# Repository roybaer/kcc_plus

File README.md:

# KCC plus - a new, enhanced, CPC6128 compatible home computer

**WORK IN PROGRESS**

The _KCC plus_ is a retroactively designed hypothetical early 1990s successor to the KC compact.
The KC compact was a largely compatible clone of the Amstrad CPC 6128, built without custom silicon.

Once completed, it can be considered a cousin of, but not a clone of the Amstrad 6128 Plus.

## Planned feature set

The following hardware features are currently planned

- Between 256 KiB and 1024 KiB of RAM, ideally as a pair of SRAM chips
- Two AY-2-8910 PSGs for additional polyphony and additional control lines, on-board Digiblaster
- 16 bit data path for pixel generation and duplication of the relevant logic for twice the color depth
- Bypassable EGA-like latch in the second RAM chip's data path to keep block fill/copy operations fast
- At least one attribute mode, e.g. for colorful high-res pseudo text modes
- Possibility to optionally double the CPU clock and/or FDC clock, if feasible
- Floppy disk and tape interface
- Internal IDE and Serial ports, if feasible
- The CPC 6128's form factor: System board should fit inside a German CPC 6128 case
- High quality keyboard with n-key rollover
- 50-pin micro ribbon expansion port
- Bi-directional 8-bit printer port (DB25)
- DIN and SCART video output and 3.5 mm audio line-out
- Two digital joystick ports
- Light pen connector
- Laser-cut case, e.g. painted plywood

## Hardware components

These hardware components have been completed

- [Keyboard assembly](kcc_plus_keyboard/README.md) using the CPC 6128 form factor

These hardware components are planned

- Feature evaluation module for CPC
  - Clock generation and audio board
  - RAM and video board
  - Mass storage board
- System board
- Laser-cut case

## License

All design files contained herein may be redistributed and/or modified under the terms of the CERN-OHL-P license.

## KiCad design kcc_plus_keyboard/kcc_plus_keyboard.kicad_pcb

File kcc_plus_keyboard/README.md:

# KCC plus - keyboard assembly

This is a mechanical keyboard for the KCC plus.
It uses a CPC 6128 compatible form factor and keyboard matrix.

# Layout

The following layout is recommended for contemporary English.
Suitable off-the-shelf keycap sets are available.

| Switch    | Glyph     | Switch    | Glyph
|:----------|:----------|:----------|:----------
| SW1       | Esc       | SW39      | F
| SW2       | 1         | SW40      | G
| SW3       | 2         | SW41      | H
| SW4       | 3         | SW42      | J
| SW5       | 4         | SW43      | K
| SW6       | 5         | SW44      | L
| SW7       | 6         | SW45      | ;
| SW8       | 7         | SW46      | '
| SW9       | 8         | SW47      | '
| SW10      | 9         | SW48      | F1
| SW11      | 0         | SW49      | F2
| SW12      | -         | SW50      | F3
| SW13      | =         | SW51      | shift
| SW14      | backspace | SW52      | Z
| SW15      | F7        | SW53      | X
| SW16      | F8        | SW54      | C
| SW17      | F9        | SW55      | V
| SW18      | tab       | SW56      | B
| SW19      | Q         | SW57      | N
| SW20      | W         | SW58      | M
| SW21      | E         | SW59      | ,
| SW22      | R         | SW60      | .
| SW23      | T         | SW61      | /
| SW24      | Y         | SW62      | \
| SW25      | U         | SW63      | shift
| SW26      | I         | SW64      | F10
| SW27      | O         | SW65      | ↑ (up)
| SW28      | P         | SW66      | .
| SW29      | [         | SW67      | control
| SW30      | ]         | SW68      | option
| SW31      | return    | SW69      | command
| SW32      | F4        | SW70      | space
| SW33      | F5        | SW71      | command
| SW34      | F6        | SW72      | del
| SW35      | capslock  | SW73      | enter
| SW36      | A         | SW74      | ← (left)
| SW37      | S         | SW75      | ↓ (down)
| SW38      | D         | SW76      | → (right)

## Pictures

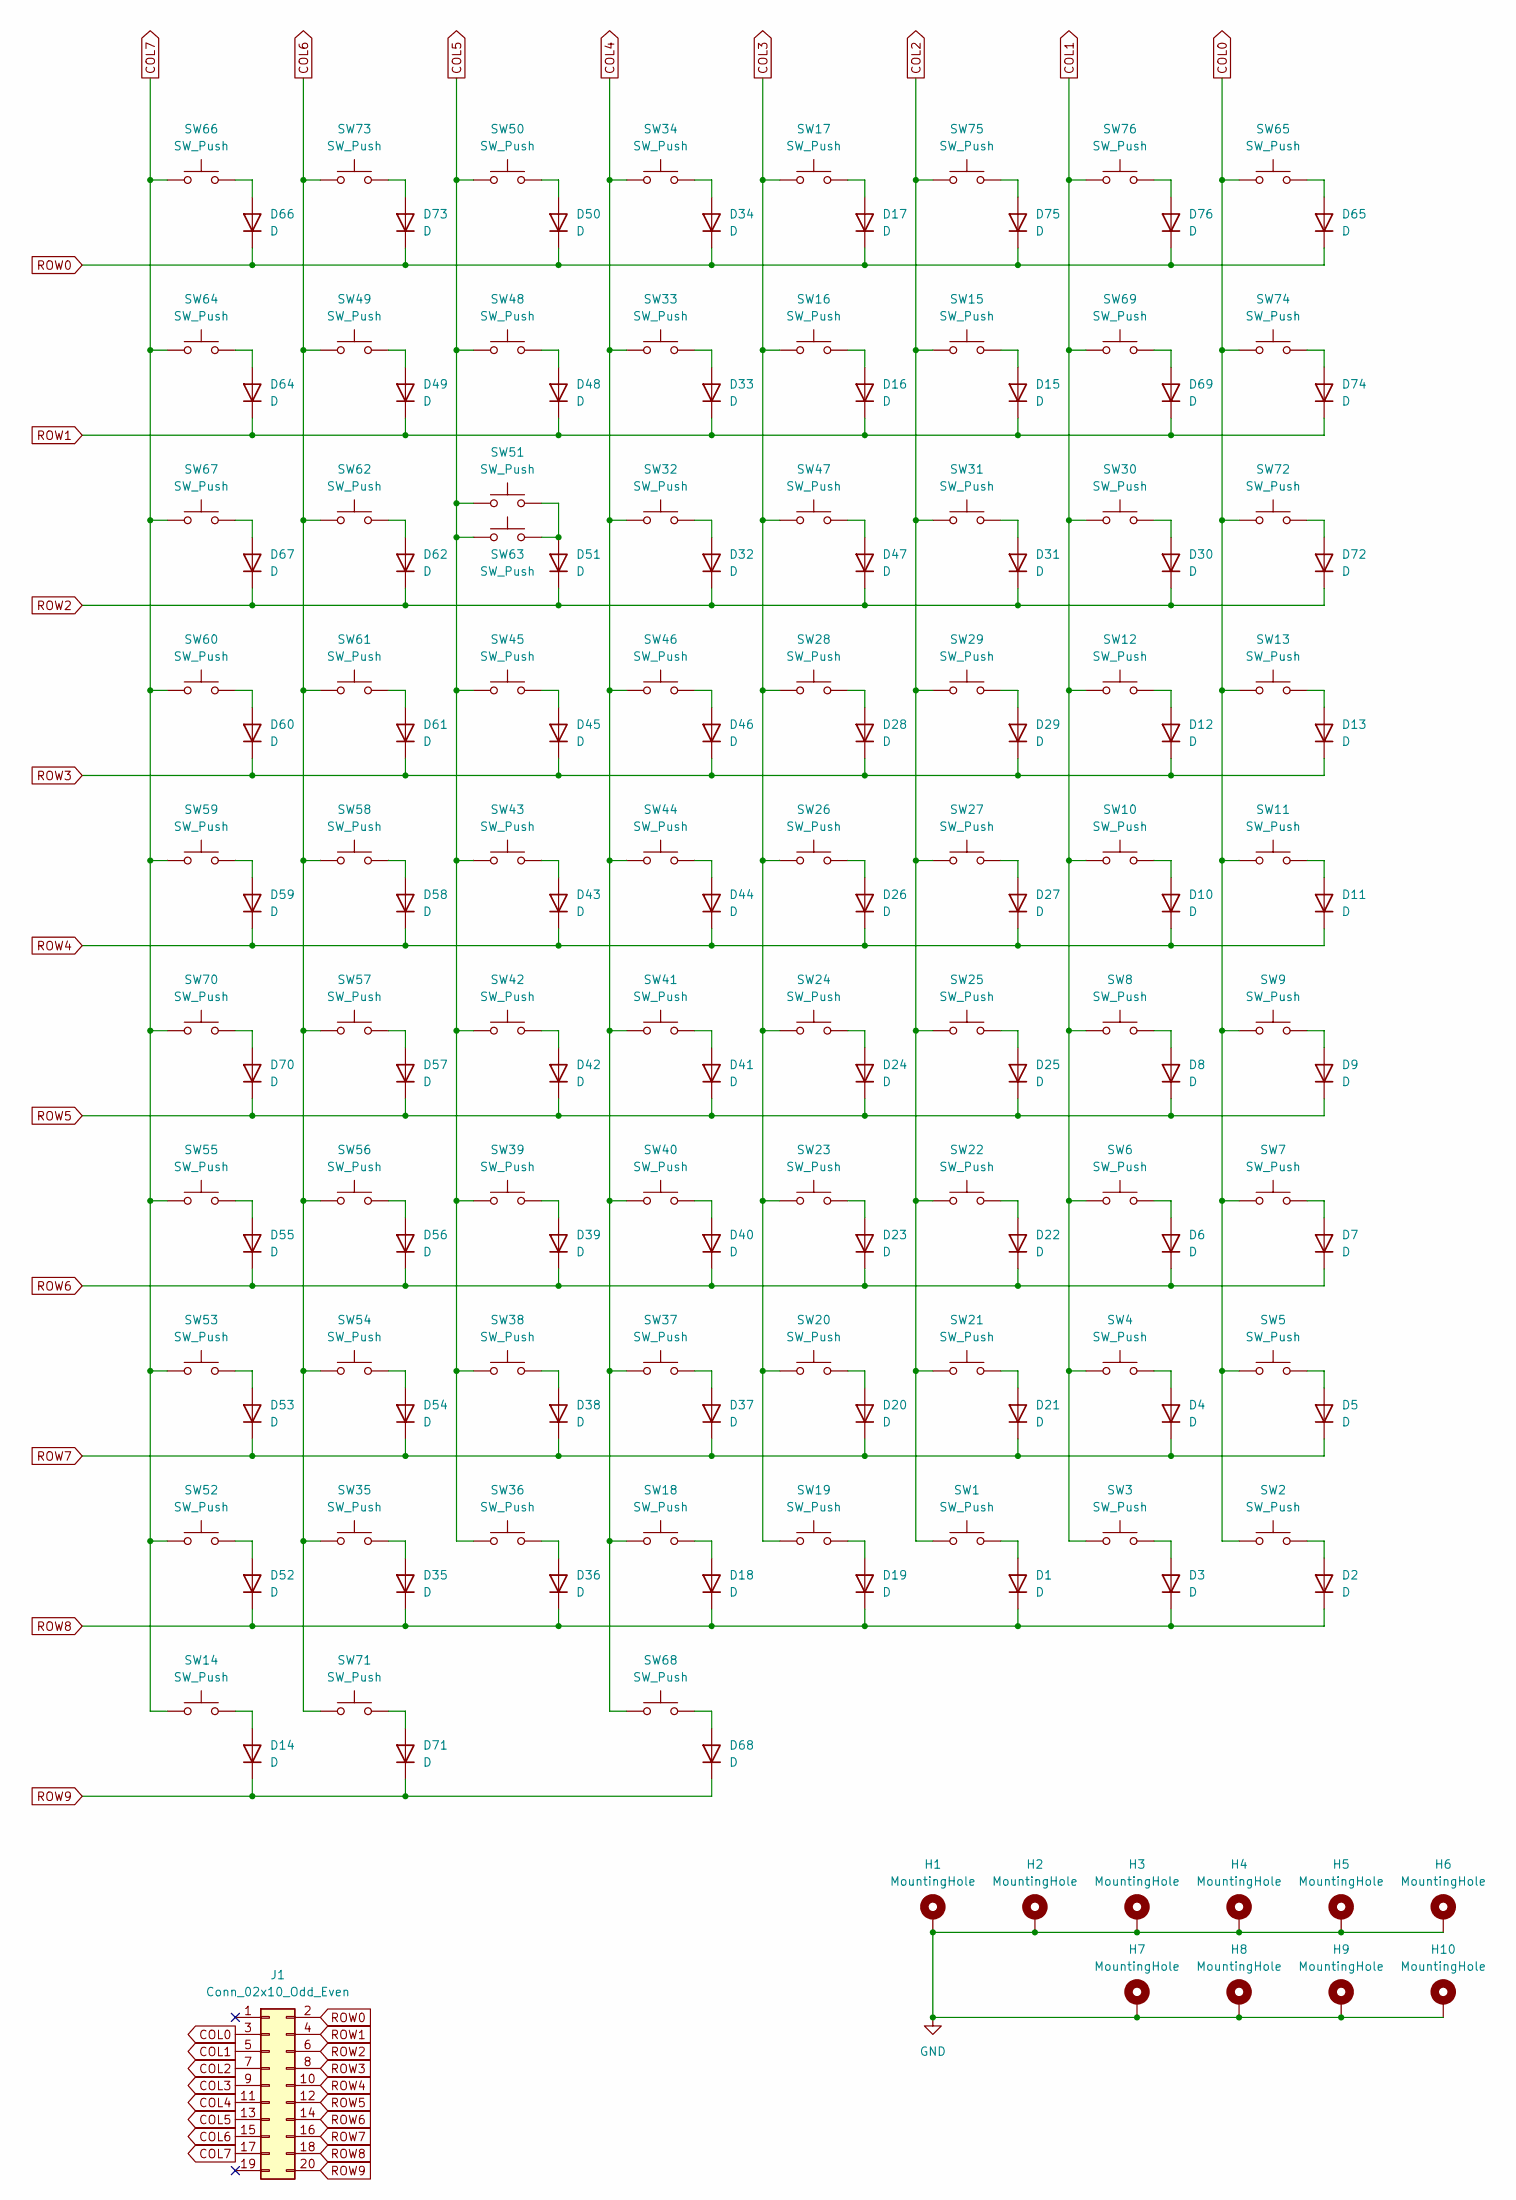
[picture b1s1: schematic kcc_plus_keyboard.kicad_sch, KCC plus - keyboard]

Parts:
D1, D2, D3, D4, D5, D6, D7, D8, D9, D10, D11, D12, D13, D14, D15, D16, D17, D18, D19, D20, D21, D22, D23, D24, D25, D26, D27, D28, D29, D30, D31, D32, D33, D34, D35, D36, D37, D38, D39, D40, D41, D42, D43, D44, D45, D46, D47, D48, D49, D50, D51, D52, D53, D54, D55, D56, D57, D58, D59, D60, D61, D62, D64, D65, D66, D67, D68, D69, D70, D71, D72, D73, D74, D75, D76: D; D_DO-35_SOD27_P7.62mm_Horizontal
H1, H3, H4, H6: MountingHole; MountingHole_4.3x6.2mm_M4_Pad_Via
H2, H5, H7, H8, H9, H10: MountingHole; MountingHole_4.3mm_M4_Pad_Via
J1: Conn_02x10_Odd_Even; PinHeader_2x10_P2.54mm_Horizontal
SW1, SW2, SW3, SW4, SW5, SW6, SW7, SW8, SW9, SW10, SW11, SW12, SW13, SW15, SW16, SW17, SW19, SW20, SW21, SW22, SW23, SW24, SW25, SW26, SW27, SW28, SW29, SW30, SW32, SW33, SW34, SW36, SW37, SW38, SW39, SW40, SW41, SW42, SW43, SW44, SW45, SW46, SW47, SW48, SW49, SW50, SW52, SW53, SW54, SW55, SW56, SW57, SW58, SW59, SW60, SW61, SW62, SW64, SW65, SW66, SW72, SW74, SW75, SW76: SW_Push; SW_Cherry_MX_1.00u_PCB
SW14: SW_Push; SW_Cherry_MX_2.00u_PCB
SW18, SW69, SW71: SW_Push; SW_Cherry_MX_1.50u_PCB
SW31: SW_Push; SW_Cherry_MX_ISOEnter_PCB
SW35, SW63: SW_Push; SW_Cherry_MX_1.75u_PCB
SW51, SW73: SW_Push; SW_Cherry_MX_2.25u_PCB
SW67, SW68: SW_Push; SW_Cherry_MX_1.25u_PCB
SW70: SW_Push; SW_Cherry_MX_6.25u_PCB

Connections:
COL0: J1.3, SW2.1, SW5.1, SW7.1, SW9.1, SW11.1, SW13.1, SW65.1, SW72.1, SW74.1
COL1: J1.5, SW3.1, SW4.1, SW6.1, SW8.1, SW10.1, SW12.1, SW30.1, SW69.1, SW76.1
COL2: J1.7, SW1.1, SW15.1, SW21.1, SW22.1, SW25.1, SW27.1, SW29.1, SW31.1, SW75.1
COL3: J1.9, SW16.1, SW17.1, SW19.1, SW20.1, SW23.1, SW24.1, SW26.1, SW28.1, SW47.1
COL4: J1.11, SW18.1, SW32.1, SW33.1, SW34.1, SW37.1, SW40.1, SW41.1, SW44.1, SW46.1, SW68.1
COL5: J1.13, SW36.1, SW38.1, SW39.1, SW42.1, SW43.1, SW45.1, SW48.1, SW50.1, SW51.1, SW63.1
COL6: J1.15, SW35.1, SW49.1, SW54.1, SW56.1, SW57.1, SW58.1, SW61.1, SW62.1, SW71.1, SW73.1
COL7: J1.17, SW14.1, SW52.1, SW53.1, SW55.1, SW59.1, SW60.1, SW64.1, SW66.1, SW67.1, SW70.1
GND: H1.1, H2.1, H3.1, H4.1, H5.1, H6.1, H7.1, H8.1, H9.1, H10.1
unnamed: D1.2 (A), SW1.2
unnamed: D2.2 (A), SW2.2
unnamed: D3.2 (A), SW3.2
unnamed: D4.2 (A), SW4.2
unnamed: D5.2 (A), SW5.2
unnamed: D6.2 (A), SW6.2
unnamed: D7.2 (A), SW7.2
unnamed: D8.2 (A), SW8.2
unnamed: D9.2 (A), SW9.2
unnamed: D10.2 (A), SW10.2
unnamed: D11.2 (A), SW11.2
unnamed: D12.2 (A), SW12.2
unnamed: D13.2 (A), SW13.2
unnamed: D14.2 (A), SW14.2
unnamed: D15.2 (A), SW15.2
unnamed: D16.2 (A), SW16.2
unnamed: D17.2 (A), SW17.2
unnamed: D18.2 (A), SW18.2
unnamed: D19.2 (A), SW19.2
unnamed: D20.2 (A), SW20.2
unnamed: D21.2 (A), SW21.2
unnamed: D22.2 (A), SW22.2
unnamed: D23.2 (A), SW23.2
unnamed: D24.2 (A), SW24.2
unnamed: D25.2 (A), SW25.2
unnamed: D26.2 (A), SW26.2
unnamed: D27.2 (A), SW27.2
unnamed: D28.2 (A), SW28.2
unnamed: D29.2 (A), SW29.2
unnamed: D30.2 (A), SW30.2
unnamed: D31.2 (A), SW31.2
unnamed: D32.2 (A), SW32.2
unnamed: D33.2 (A), SW33.2
unnamed: D34.2 (A), SW34.2
unnamed: D35.2 (A), SW35.2
unnamed: D36.2 (A), SW36.2
unnamed: D37.2 (A), SW37.2
unnamed: D38.2 (A), SW38.2
unnamed: D39.2 (A), SW39.2
unnamed: D40.2 (A), SW40.2
unnamed: D41.2 (A), SW41.2
unnamed: D42.2 (A), SW42.2
unnamed: D43.2 (A), SW43.2
unnamed: D44.2 (A), SW44.2
unnamed: D45.2 (A), SW45.2
unnamed: D46.2 (A), SW46.2
unnamed: D47.2 (A), SW47.2
unnamed: D48.2 (A), SW48.2
unnamed: D49.2 (A), SW49.2
unnamed: D50.2 (A), SW50.2
unnamed: D51.2 (A), SW51.2, SW63.2
unnamed: D52.2 (A), SW52.2
unnamed: D53.2 (A), SW53.2
unnamed: D54.2 (A), SW54.2
unnamed: D55.2 (A), SW55.2
unnamed: D56.2 (A), SW56.2
unnamed: D57.2 (A), SW57.2
unnamed: D58.2 (A), SW58.2
unnamed: D59.2 (A), SW59.2
unnamed: D60.2 (A), SW60.2
unnamed: D61.2 (A), SW61.2
unnamed: D62.2 (A), SW62.2
unnamed: D64.2 (A), SW64.2
unnamed: D65.2 (A), SW65.2
unnamed: D66.2 (A), SW66.2
unnamed: D67.2 (A), SW67.2
unnamed: D68.2 (A), SW68.2
unnamed: D69.2 (A), SW69.2
unnamed: D70.2 (A), SW70.2
unnamed: D71.2 (A), SW71.2
unnamed: D72.2 (A), SW72.2
unnamed: D73.2 (A), SW73.2
unnamed: D74.2 (A), SW74.2
unnamed: D75.2 (A), SW75.2
unnamed: D76.2 (A), SW76.2
ROW0: D17.1 (K), D34.1 (K), D50.1 (K), D65.1 (K), D66.1 (K), D73.1 (K), D75.1 (K), D76.1 (K), J1.2
ROW1: D15.1 (K), D16.1 (K), D33.1 (K), D48.1 (K), D49.1 (K), D64.1 (K), D69.1 (K), D74.1 (K), J1.4
ROW2: D30.1 (K), D31.1 (K), D32.1 (K), D47.1 (K), D51.1 (K), D62.1 (K), D67.1 (K), D72.1 (K), J1.6
ROW3: D12.1 (K), D13.1 (K), D28.1 (K), D29.1 (K), D45.1 (K), D46.1 (K), D60.1 (K), D61.1 (K), J1.8
ROW4: D10.1 (K), D11.1 (K), D26.1 (K), D27.1 (K), D43.1 (K), D44.1 (K), D58.1 (K), D59.1 (K), J1.10
ROW5: D8.1 (K), D9.1 (K), D24.1 (K), D25.1 (K), D41.1 (K), D42.1 (K), D57.1 (K), D70.1 (K), J1.12
ROW6: D6.1 (K), D7.1 (K), D22.1 (K), D23.1 (K), D39.1 (K), D40.1 (K), D55.1 (K), D56.1 (K), J1.14
ROW7: D4.1 (K), D5.1 (K), D20.1 (K), D21.1 (K), D37.1 (K), D38.1 (K), D53.1 (K), D54.1 (K), J1.16
ROW8: D1.1 (K), D2.1 (K), D3.1 (K), D18.1 (K), D19.1 (K), D35.1 (K), D36.1 (K), D52.1 (K), J1.18
ROW9: D14.1 (K), D68.1 (K), D71.1 (K), J1.20

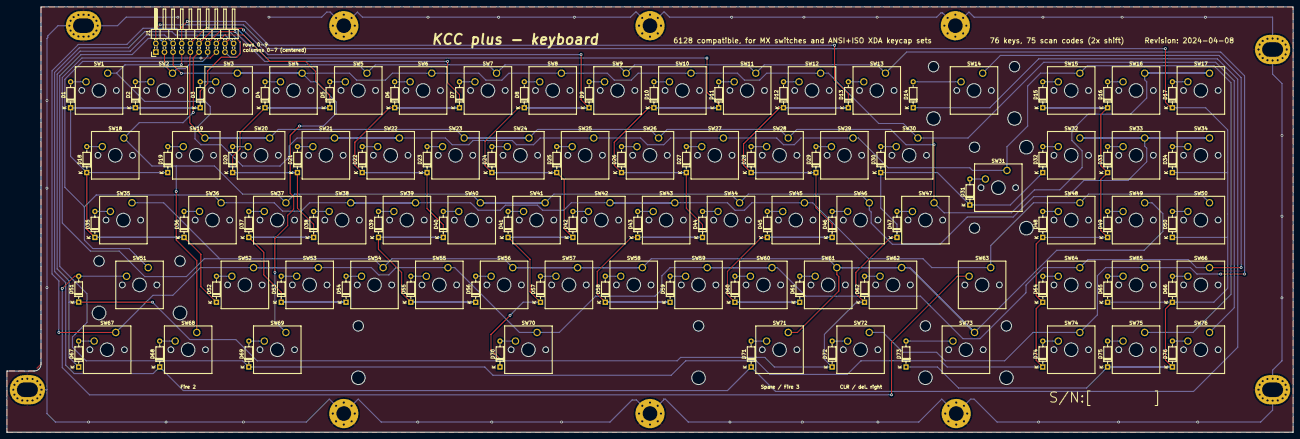
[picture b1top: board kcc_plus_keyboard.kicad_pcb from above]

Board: 2 copper layers, 378.0 x 125.0 mm, 162 parts (0 on the bottom side), 94 nets.

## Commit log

2024-04-08 initial board version
2024-04-08 move three diodes away from stabilizers
2024-05-13 add documentation
